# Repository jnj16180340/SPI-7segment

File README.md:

# SPI-7segment
An 8x7segment display that communicates over SPI

The 2x4digit displays are "LD-3461AS," which measure 14mmx30mm.

This is intended for LaenPCB (OSH Park etc). If you need a single layer board, be aware that it will have several jumpers.

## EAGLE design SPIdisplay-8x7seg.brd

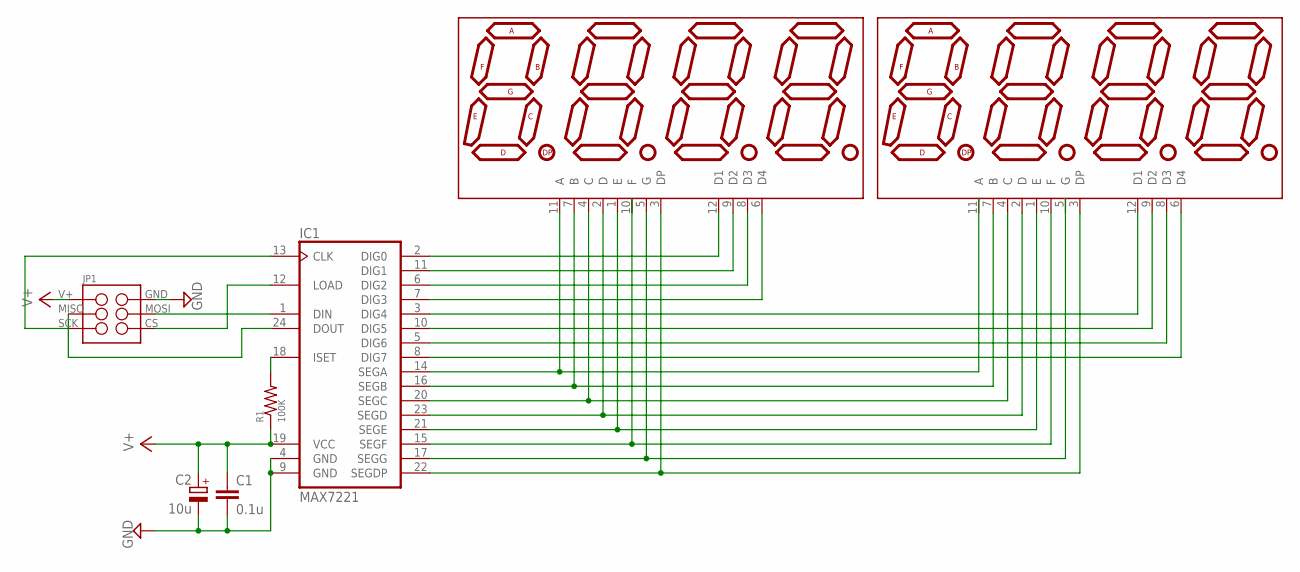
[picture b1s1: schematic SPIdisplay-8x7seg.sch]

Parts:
C1: 0.1u; C050-025X075
C2: 10u; E2,5-5
DISP1, DISP2: 7-SEG-4DIG-LD-3461AS-HP-BUBBLE; DIL12
IC1: MAX7221; DIL24-3
JP1: M03X2SHROUD; 2X3-SPI-SHROUDED
R1: 100K; 0207/10

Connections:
GND: C1.2, C2.-, IC1.4 (GND), IC1.9 (GND), JP1.2
unnamed: IC1.1 (DIN), JP1.4
unnamed: IC1.12 (LOAD), JP1.6
unnamed: IC1.13 (CLK), JP1.5
unnamed: IC1.24 (DOUT), JP1.3
unnamed: IC1.18 (ISET), R1.2
unnamed: DISP1.12 (D1), IC1.2 (DIG0)
unnamed: DISP1.9 (D2), IC1.11 (DIG1)
unnamed: DISP1.8 (D3), IC1.6 (DIG2)
unnamed: DISP1.6 (D4), IC1.7 (DIG3)
unnamed: DISP2.12 (D1), IC1.3 (DIG4)
unnamed: DISP2.9 (D2), IC1.10 (DIG5)
unnamed: DISP2.8 (D3), IC1.5 (DIG6)
unnamed: DISP2.6 (D4), IC1.8 (DIG7)
unnamed: DISP1.11 (A), IC1.14 (SEGA)
unnamed: DISP1.7 (B), DISP2.7 (B), IC1.16 (SEGB)
unnamed: DISP1.4 (C), DISP2.4 (C), IC1.20 (SEGC)
unnamed: DISP1.2 (D), DISP2.2 (D), IC1.23 (SEGD)
unnamed: DISP1.1 (E), DISP2.1 (E), IC1.21 (SEGE)
unnamed: DISP2.10 (F), IC1.15 (SEGF)
unnamed: DISP1.5 (G), IC1.17 (SEGG)
unnamed: DISP1.3 (DP), DISP2.3 (DP), IC1.22 (SEGDP)
V+: C1.1, C2.+, IC1.19 (VCC), JP1.1, R1.1

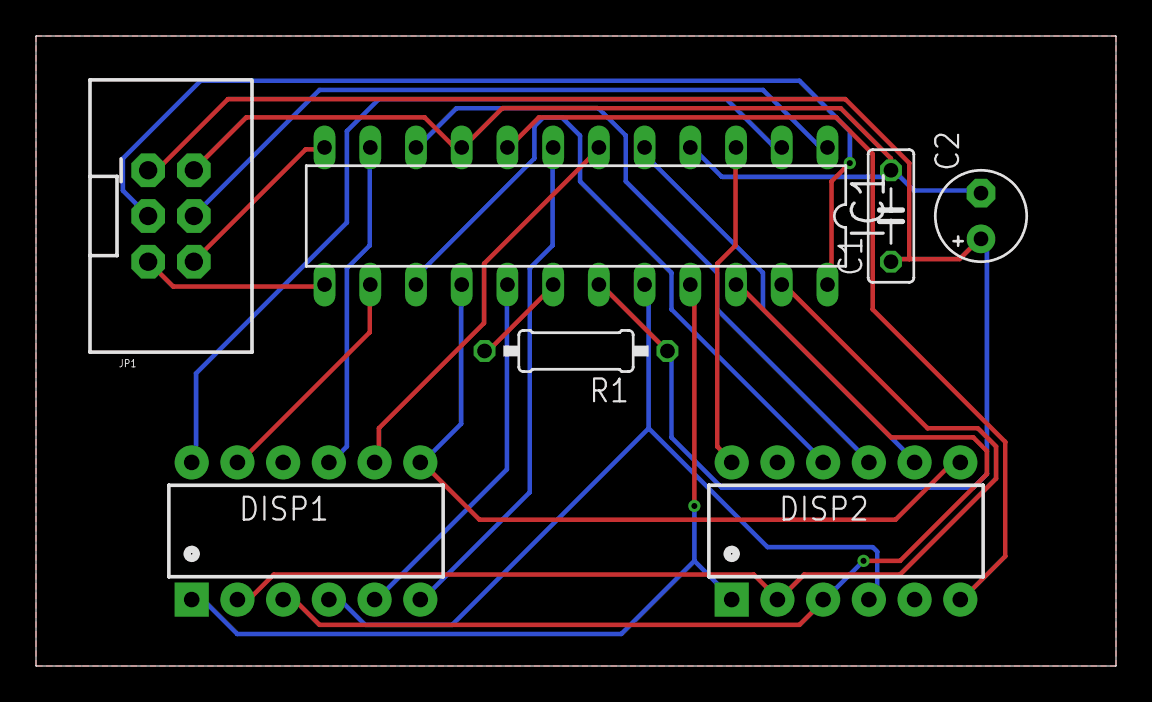
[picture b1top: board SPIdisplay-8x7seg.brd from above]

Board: 2 copper layers, 60.0 x 35.0 mm, 7 parts (0 on the bottom side), 23 nets.

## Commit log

2015-02-04 nate johnson edits
2015-02-04 added PCB
2015-02-04 nate johnson explains

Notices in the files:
parts and their libraries:
SparkFun-Displays: Licensing: Creative Commons ShareAlike 4.0 International - https://creativecommons.org/licenses/by-sa/4.0
